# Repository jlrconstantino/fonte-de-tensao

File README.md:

## PROJETO FONTE DE TENSÃO ELÉTRICA

Trabalho desenvolvido para a disciplina de Eletrônica para Computação; curso regular de graduação em Bacharelado em Ciências de Computação — ICMC-USP. São responsáveis pelo seu desenvolvimento: João Lucas Rodrigues Constantino e Gabriel Zanotim Manhani. O projeto consiste na produção de uma fonte de tensão elétrica, cujo valor absoluto varia entre, aproximadamente, 2.96 e 12.2V; ela opera com uma fonte de corrente alternada com frequência de 60.0Hz e tensão máxima igual a 127.0V.

### Arquivos de simulação pelo Falstad:

O circuito pode ser acessado por meio do link *http://tinyurl.com/y732pbrl*; caso esse não funcione, a aplicação do *Falstad*, em navegador de *internet*, utiliza um código textual para salvar e carregar seus circuitos. No caso desse projeto, tal código pode ser encontrado [aqui](falstad-code.txt). Para replicar o circuito, uma das alternativas é copiar, para a área de transferência, todo o texto contido nesse arquivo; acessar o sítio *https://www.falstad.com/circuit/*; procurar por *Arquivo* no canto superior esquerdo; ir até *Importar de Arquivo Texto...*; copiar o conteúdo para a caixa originada e, enfim, selecionar *OK*.

### Componentes eletrônicos utilizados

O resistor de 120.0Ω e o voltímetro são meramente ilustrativos, servindo somente aos propósitos de simulação e de análise, logo, não integram o circuito final. Ademais, o LED e o resistor de 1.0kΩ a ele associado são componentes opcionais.

Nome do componente | Especificações | Preço estimado |
--- | --- | --- |
Transformador | Razão 1:5 ou 24.0V; 200.0mA | R$23.99 |
Ponte retificadora | 800.0mA | R$0.82 |
Capacitor eletrolítico | 470.0µF; 30.0V | R$0.90 |
Resistor (LED) | 2.0kΩ | R$0.17 |
Resistor (diodo zener) | 2.2KΩ | R$0.22 |
Resistor (potenciômetro) | 2.2kΩ | R$0.22 |
Diodo emissor de luz (LED) | 20.0mA; 2.0V | R$0.20 |
Diodo zener | 30.0mA; 0.5W; z=13.0V | R$0.60 |
Potenciômetro | 5.0kΩ; 10.0V | R$1.99 |
Transistor NPN | 30.0mA; 30.0V | R$0.24 |

### Arquivos esquemáticos: circuito isolado e placa de circuito impresso

Os arquivos esquemáticos do *Eagle* são de extensões exclusivas à sua interpretação e, portanto, somente podem ser acessadas por meio de uma versão compatível desse programa. A saber, o sítio digital oficial desse *software* se encontra em *https://www.autodesk.com/products/eagle/*. Acima, está uma imagem da captura do resultado final do esquema do circuito, cujo arquivo correspondente, de extensão *.sch*, pode ser obtido [aqui](eagle-schematic-file.sch). Abaixo, há uma imagem do esquema da placa de circuito impresso, que representa as dimensões e disposições finais dos componentes e dos fios em uma placa desse tipo, cujo arquivo correspondente, de extensão *.brd*, é obtível por meio deste *[link](eagle-schematic-file.brd)*.

### Análise da funcionalidade e das especificações dos componentes

Um vídeo explicativo está disponível, embora desatualizado, e pode ser acessado por meio do *link* *https://youtu.be/DKq6uI3zoWM*. Como já afirmado, o circuito opera com uma fonte de corrente alternada, cujas especificações são uma frequência de 60.0Hz e um módulo máximo de tensão elétrica igual a 127.0V, todavia, caso um transformador de voltagem dupla seja implementado, tal fonte pode passar a receber um módulo máximo de 220.0V.

O **transformador** reduz a oscilação de tensão elétrica, originalmente estimada entre 127.0V e -127.0V, para um intervalo entre 24.0V e -24.0V, o que permite a utilização de componentes menos robustos no restante do circuito, os quais são relativamente mais baratos e dissipam menor quantia energética quando em operação. Esse componente não integra a placa de circuito impresso, pois ocorre como adereço externo a ela, que se conecta diretamente ao cabeçalho de entrada. Portanto, a entrada de fato dessa placa se torna a entrada do transformador.

A **ponte retificadora**, ou ponte de diodos, limita o intervalo de oscilação da tensão elétrica para 0 a 24.0V ao impedir o tráfego de retorno da corrente elétrica, isto é, impede o sentido oposto de navegação dessa ao longo do circuito. A corrente elétrica máxima que passa por esse componente apresenta valor de, aproximadamente, 720.0mA, o que torna seguro utilizar um modelo em que a resistência máxima à corrente elétrica seja de 800.0mA.

O **capacitor eletrolítico** transforma a corrente alternada em corrente contínua, além de reduzir e atenuar a variação de tensão elétrica. Isso ocorre devido à sua alternância de estados entre um armazém de carga e uma fonte de alimentação alternativa para o restante do circuito. Uma capacitância de 220.0µF serve aos propósitos desse projeto, porém possui estabilidade ligeiramente menor do que os utilizados 470.0µF, além de que este garante uma dissipação menor de energia durante a carga.

O **LED**, isto é, diodo emissor de luz, indica visualmente quando a fonte está ou não em operação. O resistor de 2.0kΩ a ele associado promove a viabilidade da utilização de um diodo que aguente a passagem de até 20.0mA de corrente elétrica através de si.

O **diodo zener**, com voltagem terminal de 13.0V, impede que a corrente elétrica o ultrapasse caso sua tensão elétrica associada supere tal voltagem. Possui, como função,  filtrar a tensão que acessará a base do transistor NPN a seguir, além de determinar, por meio de seus 13.0V, a maior tensão elétrica ideal que a saída do circuito poderá apresentar. A saber, o resistor de 2.2KΩ associado a esse diodo torna seguro utilizar um modelo que suporte um módulo máximo de corrente elétrica igual a 30.0mA, além de reduzir a utilização de corrente elétrica nessa porção do circuito. Por ser submetido, constantemente, a cerca de -3.0mA e -13.0V, é suficiente que resista a uma potência elétrica máxima de 0.5W.

O **potenciômetro** teve suas especificações devidamente adequadas à tensão elétrica de saída do circuito. Com 25.0Ω, essa assume o valor aproximado de 2.96V e, com 5.0kΩ, o valor aproximado de 12.2V. O resistor de 2.2kΩ que vem a seguir garante que o potenciômetro seja sempre alimentado corretamente com carga elétrica.

O **transistor NPN** indica o componente final desse circuito, e se responsabiliza pela última redução de oscilação de ambas, corrente e tensão elétricas de saída. A corrente elétrica que surge por sua base possui módulo aproximado de 244.0µA, o que é transformado, pelo transistor, em cerca de 24.0mA em sua saída. Por seu coletor ser submetido, constantemente, a uma corrente elétrica de, aproximadamente, 24.0mA, é suficiente que o modelo de NPN implementado suporte a um máximo de 30.0mA. Ademais, impede que a resistência do circuito em carga, que é conectado ao cabeçalho de saída, modifique o comportamento do restante do circuito.

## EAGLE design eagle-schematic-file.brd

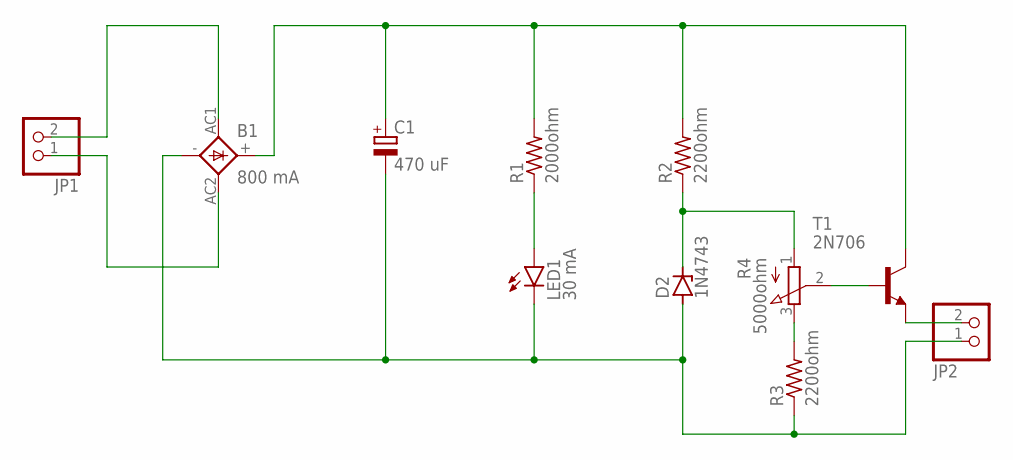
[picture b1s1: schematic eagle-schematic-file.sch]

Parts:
B1: 800 mA; 1KAB
C1: 470 uF; E3,5-10
D2: 1N4743; ZDIO12.5
JP1, JP2: PINHD-1X2; 1X02
LED1: 30 mA; LED5MM
R1: 2000ohm; 0309/12
R2, R3: 2200ohm; 0309/12
R4: 5000ohm; 3RP/1610N
T1: 2N706; TO18

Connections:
unnamed: B1.AC1, JP1.2
unnamed: B1.AC2, JP1.1
unnamed: B1.+, C1.+, R1.2, R2.2, T1.3 (C)
unnamed: B1.-, C1.-, D2.A, JP2.1, LED1.K (C), R3.1
unnamed: LED1.A, R1.1
unnamed: D2.C, R2.1, R4.1 (A)
unnamed: R3.2, R4.3 (E)
unnamed: R4.2 (S), T1.2 (B)
unnamed: JP2.2, T1.1 (E)

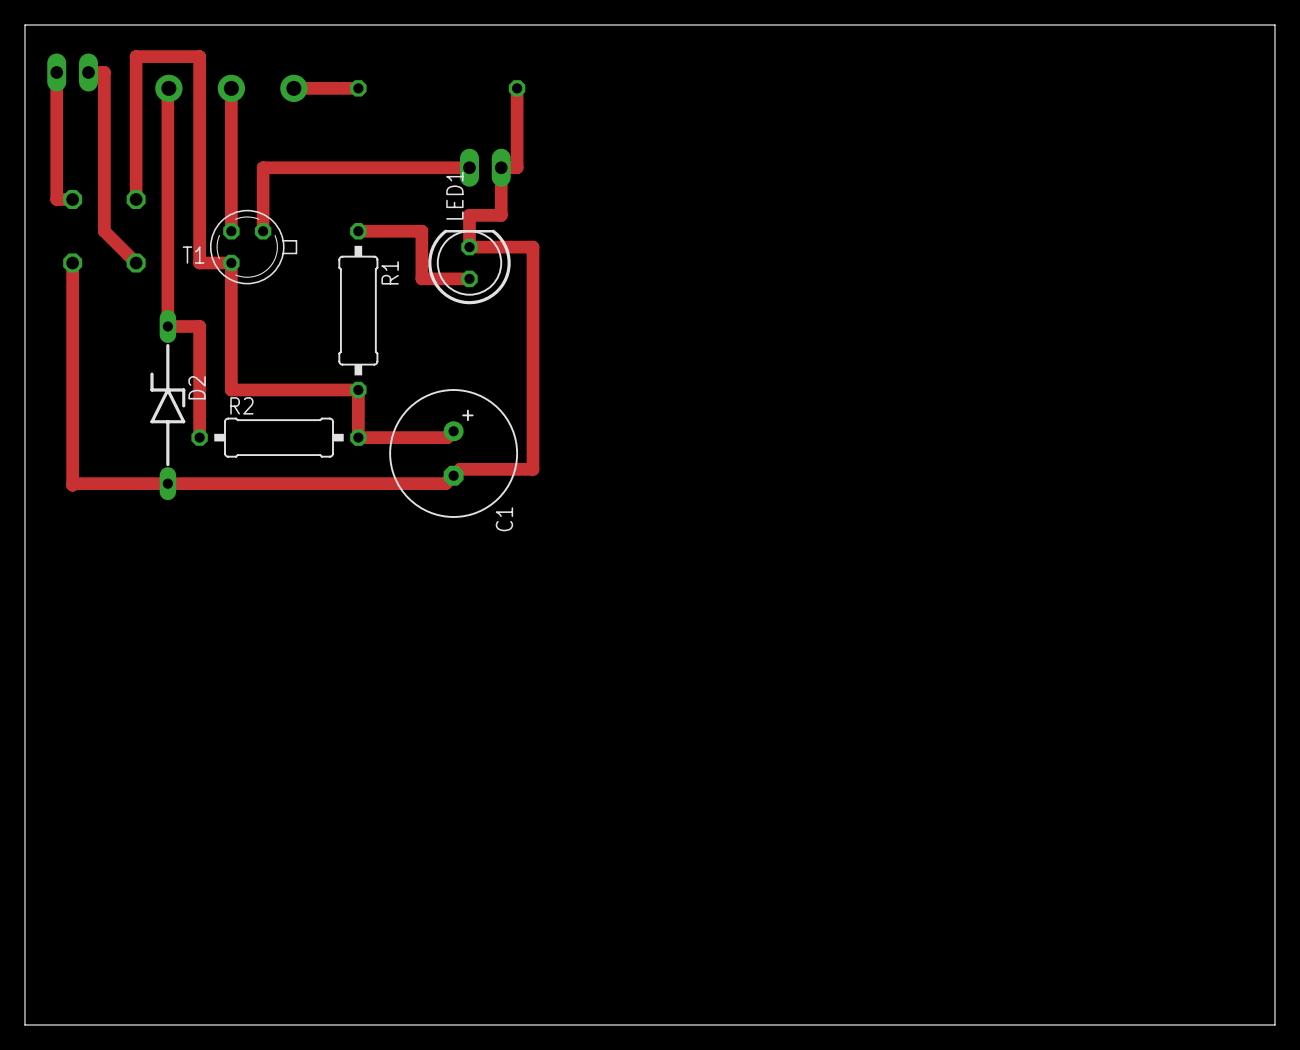
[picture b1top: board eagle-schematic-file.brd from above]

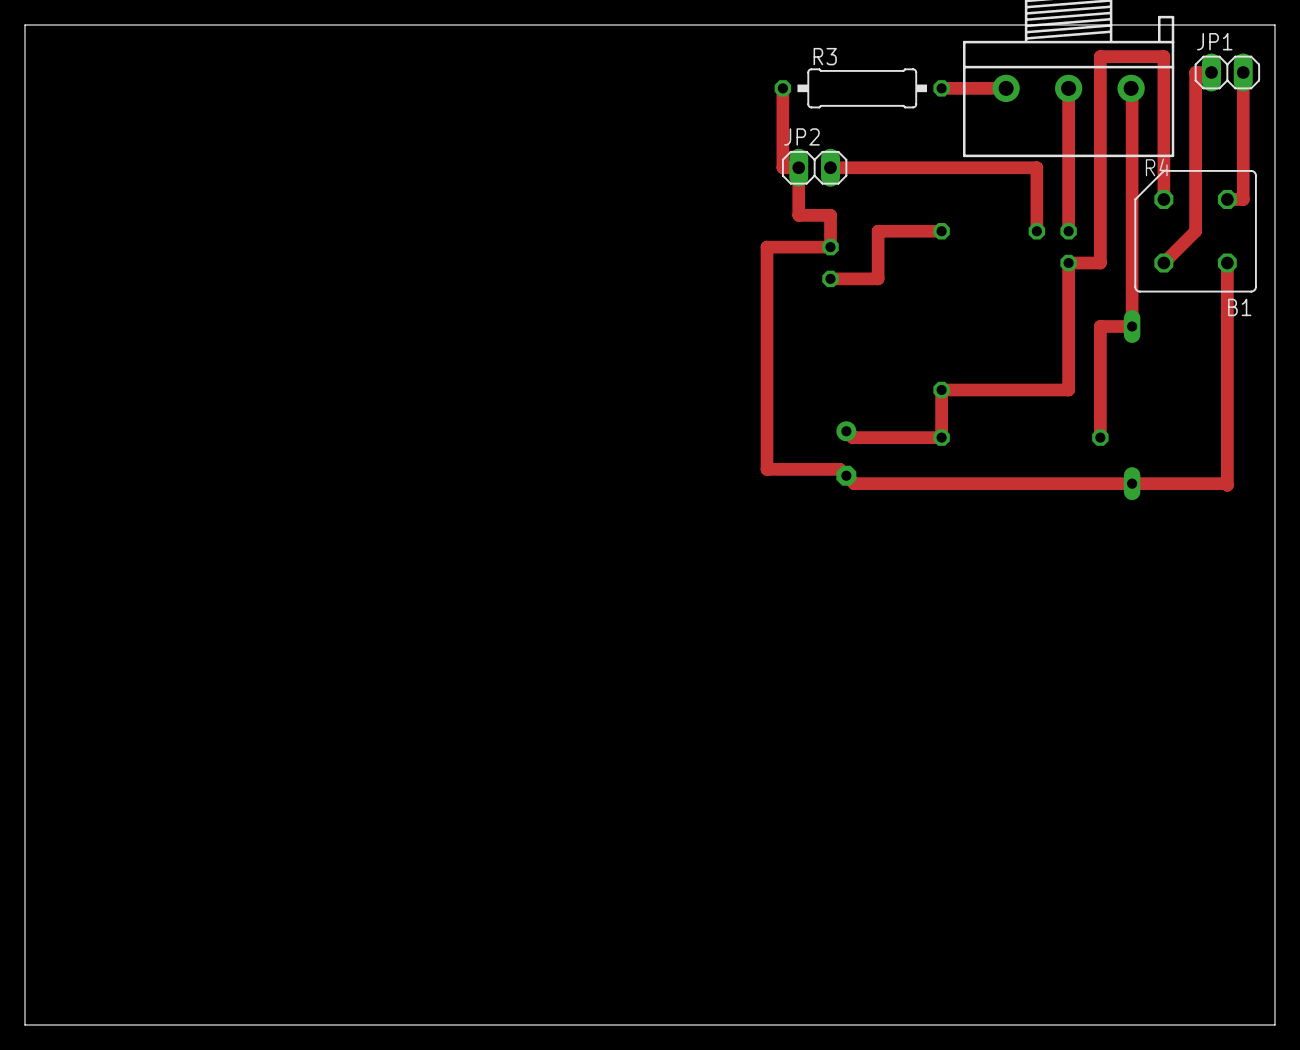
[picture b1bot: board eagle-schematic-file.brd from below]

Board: 2 copper layers, 100.0 x 80.0 mm, 11 parts (5 on the bottom side), 9 nets.
